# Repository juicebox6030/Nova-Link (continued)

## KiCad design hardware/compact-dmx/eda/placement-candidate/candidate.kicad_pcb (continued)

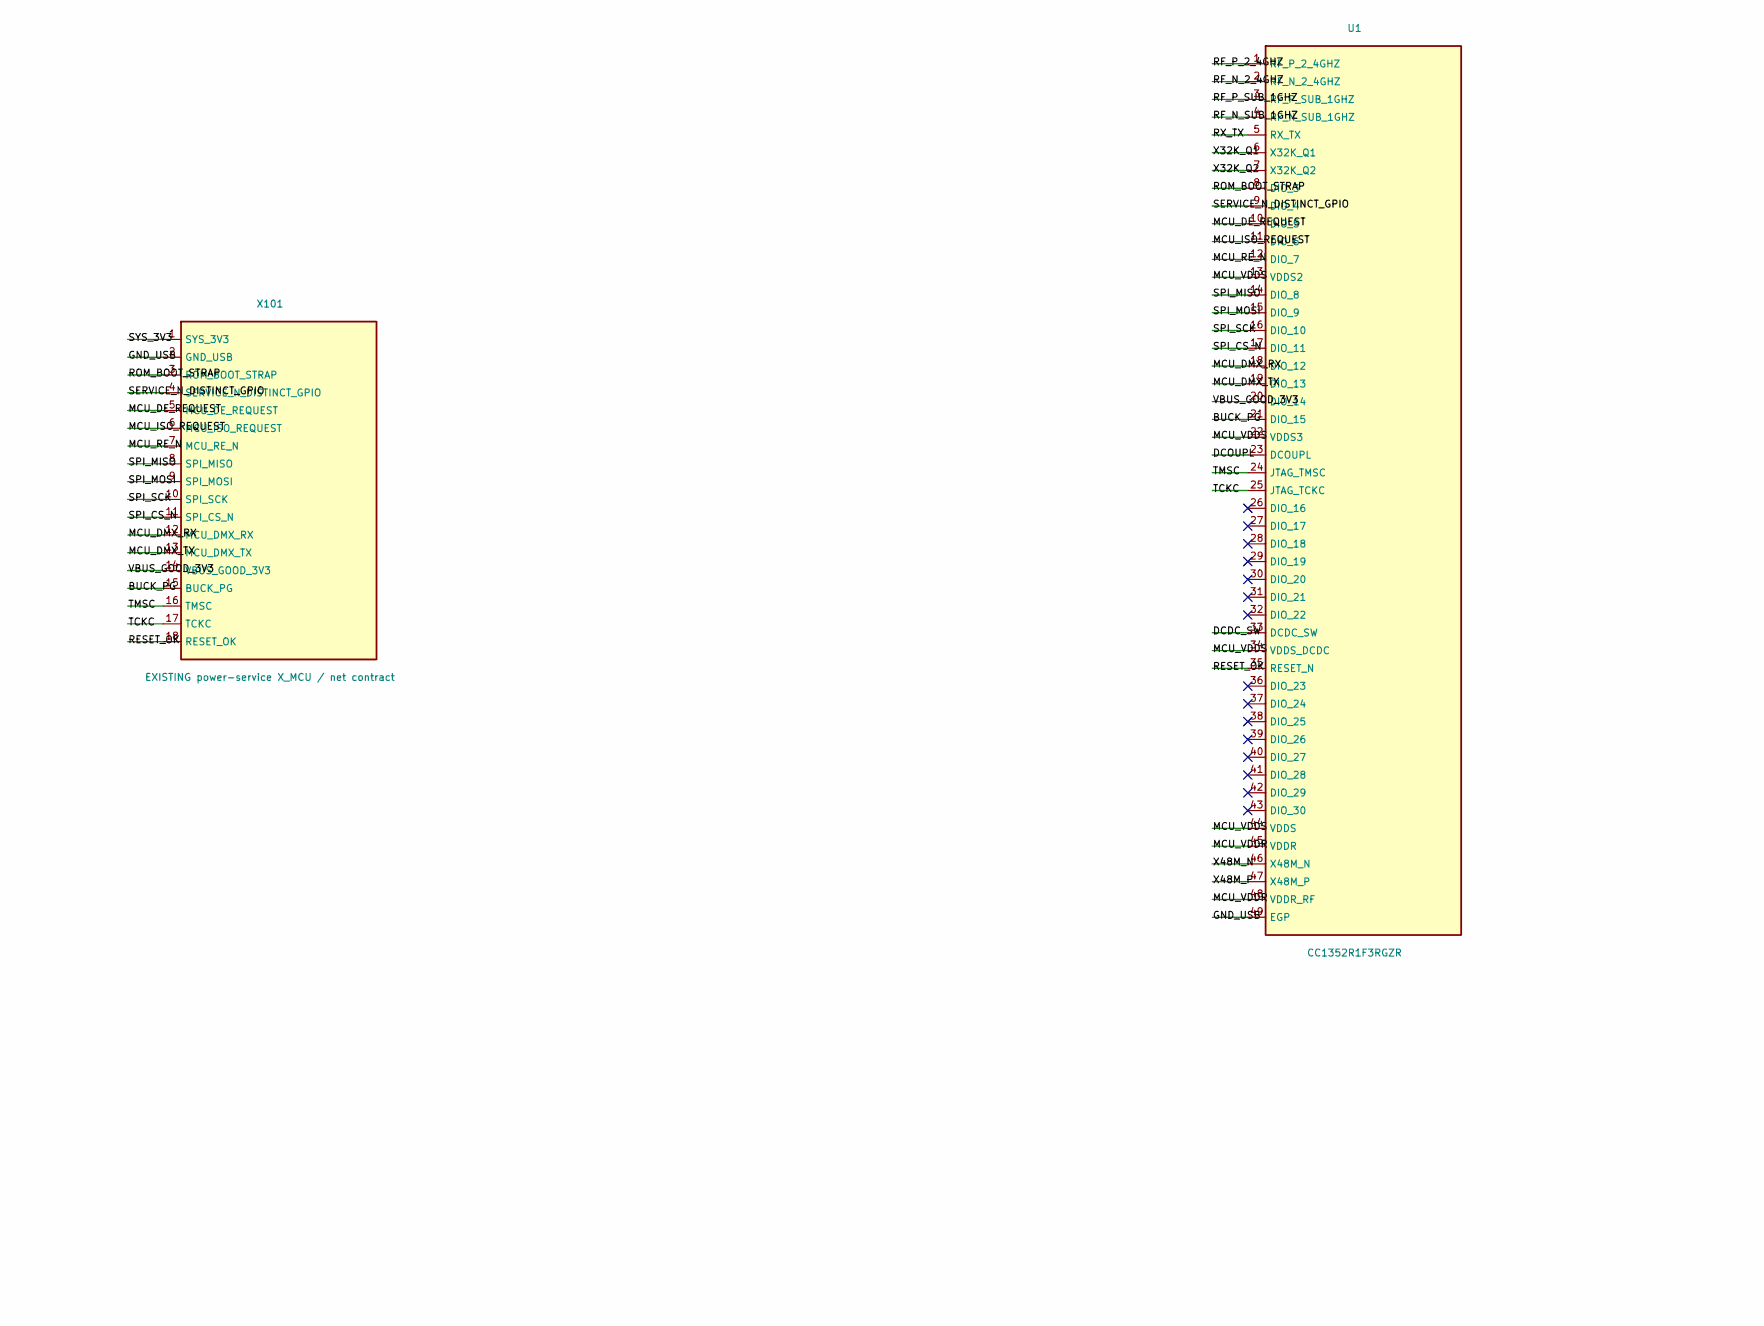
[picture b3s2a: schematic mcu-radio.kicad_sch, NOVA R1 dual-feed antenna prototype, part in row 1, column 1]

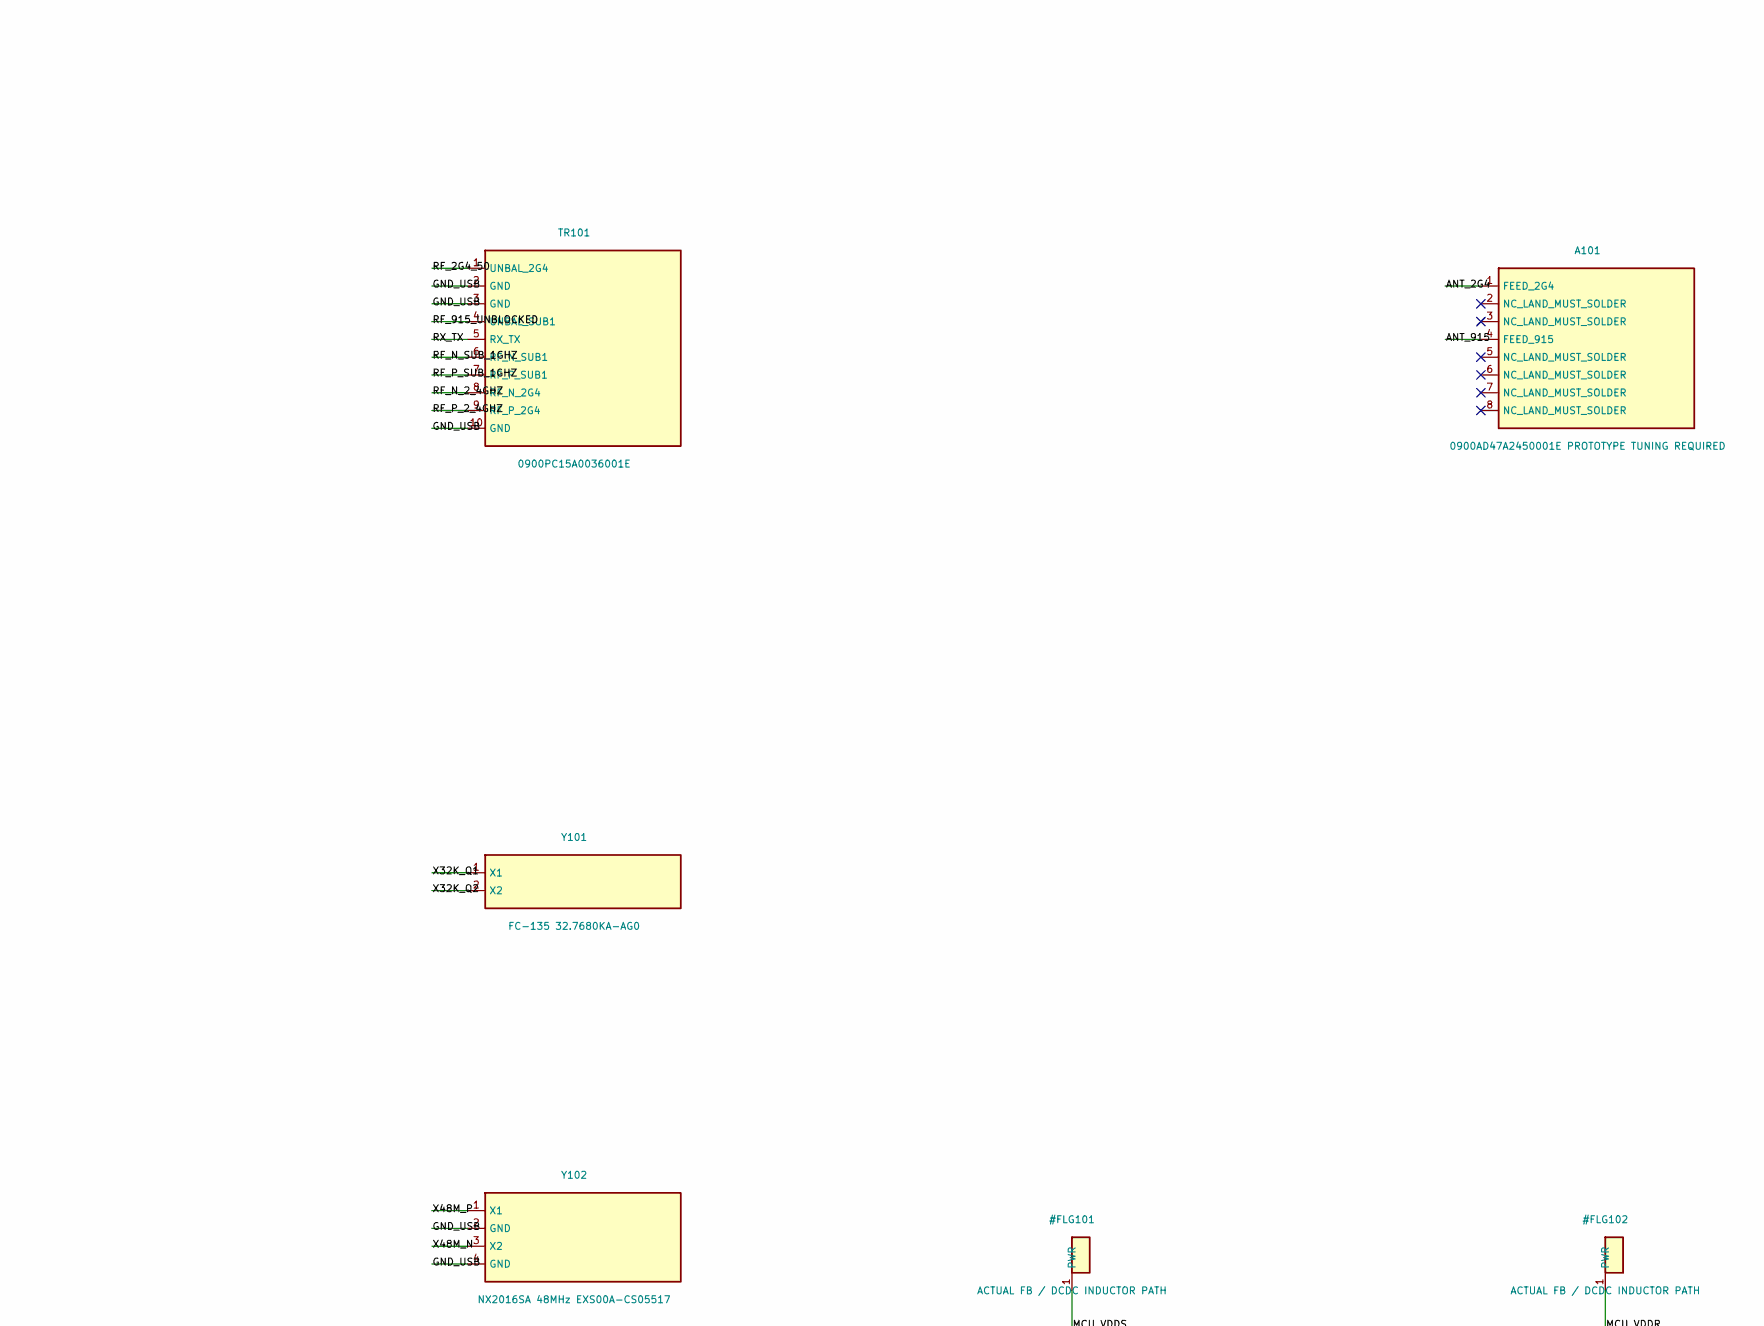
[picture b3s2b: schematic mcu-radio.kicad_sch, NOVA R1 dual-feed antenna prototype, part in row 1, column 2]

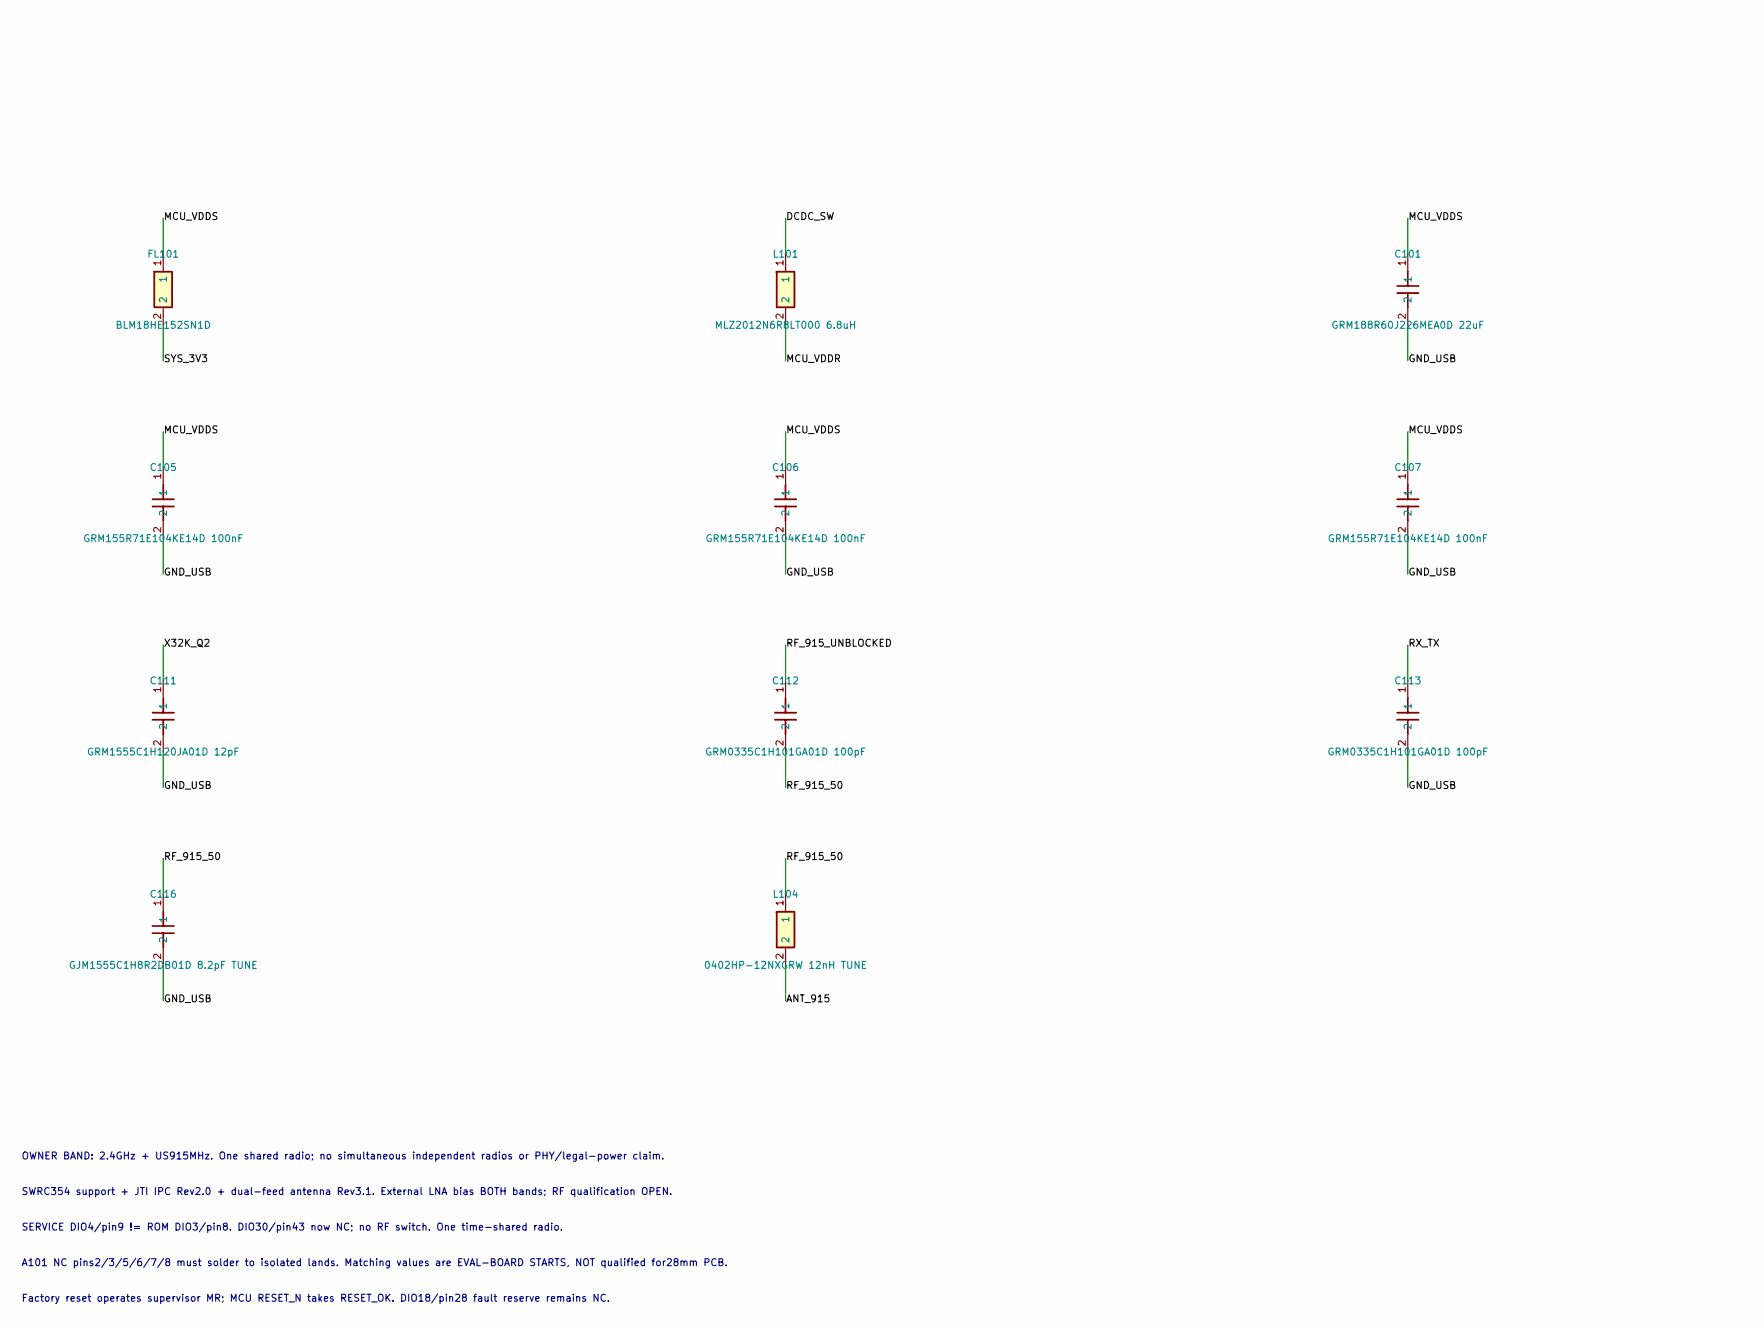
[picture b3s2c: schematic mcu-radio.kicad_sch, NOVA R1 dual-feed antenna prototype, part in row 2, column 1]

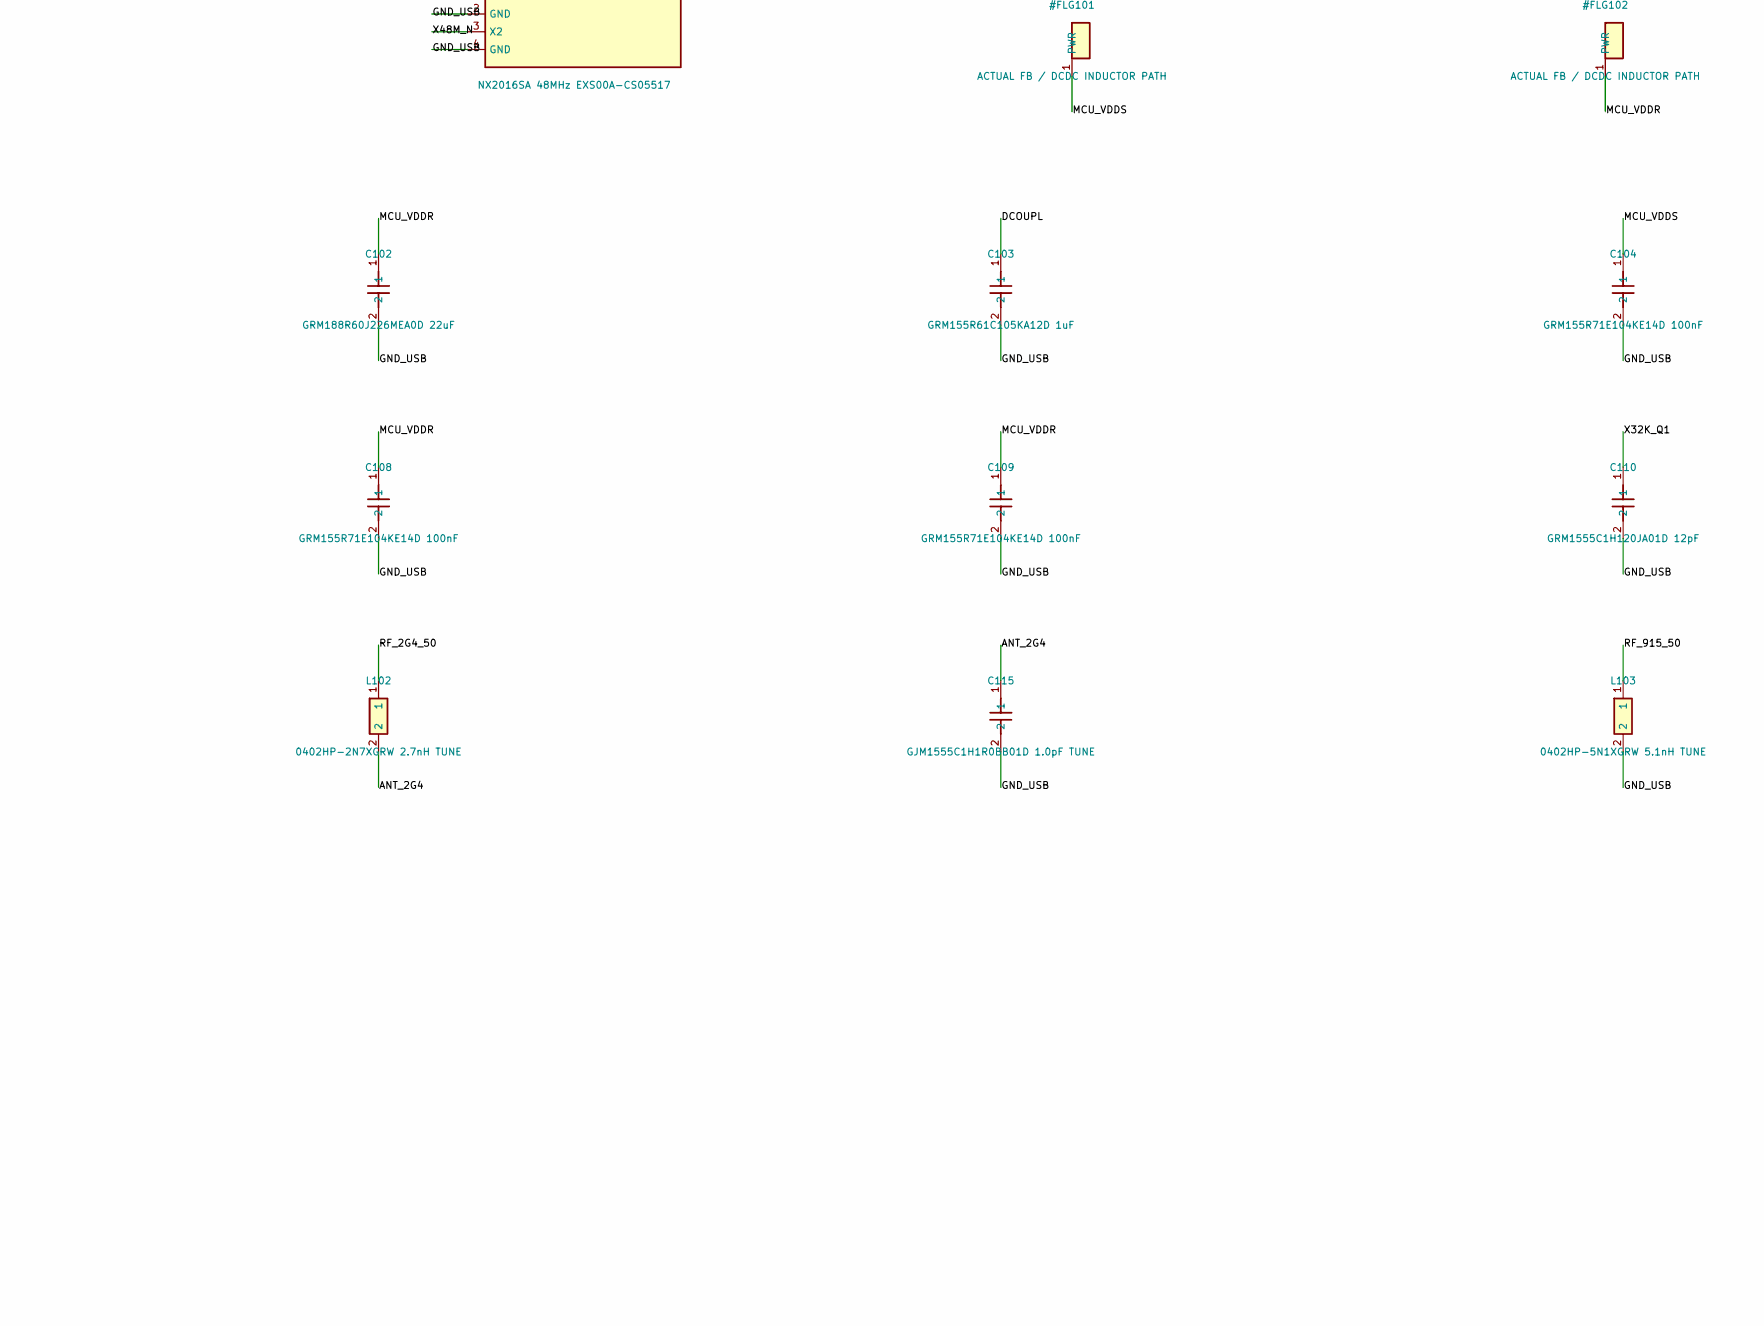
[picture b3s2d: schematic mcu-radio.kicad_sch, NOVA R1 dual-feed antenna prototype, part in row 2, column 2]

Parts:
A101: 0900AD47A2450001E PROTOTYPE TUNING REQUIRED; Johanson_0900AD47_IsolatedLands
C101, C102: GRM188R60J226MEA0D 22uF; TI_CAPC1608_Vector
C103: GRM155R61C105KA12D 1uF; TI_CAPC1005_Vector
C104, C105, C106, C107, C108, C109: GRM155R71E104KE14D 100nF; TI_CAPC1005_Vector
C110, C111: GRM1555C1H120JA01D 12pF; TI_CAPC1005_Vector
C112, C113: GRM0335C1H101GA01D 100pF; TI_CAPC0603_Vector
C115: GJM1555C1H1R0BB01D 1.0pF TUNE; Murata_GJM155_Manufacturer
C116: GJM1555C1H8R2DB01D 8.2pF TUNE; Murata_GJM155_Manufacturer
FL101: BLM18HE152SN1D; TI_BLM18_Vector
L101: MLZ2012N6R8LT000 6.8uH; TI_MLZ2012_Vector
L102: 0402HP-2N7XGRW 2.7nH TUNE; Coilcraft_0402HP_Manufacturer
L103: 0402HP-5N1XGRW 5.1nH TUNE; Coilcraft_0402HP_Manufacturer
L104: 0402HP-12NXGRW 12nH TUNE; Coilcraft_0402HP_Manufacturer
TR101: 0900PC15A0036001E; TI_IPC1352_Vector
U1: CC1352R1F3RGZR; TI_RGZ0048A
X101: EXISTING power-service X_MCU / net contract
Y101: FC-135 32.7680KA-AG0; Epson_FC135_Manufacturer
Y102: NX2016SA 48MHz EXS00A-CS05517; NDK_NX2016SA_Manufacturer

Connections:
ANT_2G4: A101.1 (FEED_2G4), C115.1, L102.2
ANT_915: A101.4 (FEED_915), L104.2
BUCK_PG: U1.21 (DIO_15), X101.15 (BUCK_PG)
DCDC_SW: L101.1, U1.33 (DCDC_SW)
DCOUPL: C103.1, U1.23 (DCOUPL)
GND_USB: C101.2, C102.2, C103.2, C104.2, C105.2, C106.2, C107.2, C108.2, C109.2, C110.2, C111.2, C113.2, C115.2, C116.2, L103.2, TR101.2 (GND), TR101.3 (GND), TR101.10 (GND), U1.49 (EGP), X101.2 (GND_USB), Y102.2 (GND), Y102.4 (GND); also elsewhere on the board
MCU_DE_REQUEST: U1.10 (DIO_5), X101.5 (MCU_DE_REQUEST)
MCU_DMX_RX: U1.18 (DIO_12), X101.12 (MCU_DMX_RX); also elsewhere on the board
MCU_DMX_TX: U1.19 (DIO_13), X101.13 (MCU_DMX_TX); also elsewhere on the board
MCU_ISO_REQUEST: U1.11 (DIO_6), X101.6 (MCU_ISO_REQUEST)
MCU_RE_N: U1.12 (DIO_7), X101.7 (MCU_RE_N); also elsewhere on the board
MCU_VDDR: C102.1, C108.1, C109.1, L101.2, U1.45 (VDDR), U1.48 (VDDR_RF)
MCU_VDDS: C101.1, C104.1, C105.1, C106.1, C107.1, FL101.1, U1.13 (VDDS2), U1.22 (VDDS3), U1.34 (VDDS_DCDC), U1.44 (VDDS)
RESET_OK: U1.35 (RESET_N), X101.18 (RESET_OK)
RF_2G4_50: L102.1, TR101.1 (UNBAL_2G4)
RF_915_50: C112.2, C116.1, L103.1, L104.1
RF_915_UNBLOCKED: C112.1, TR101.4 (UNBAL_SUB1)
RF_N_2_4GHZ: TR101.8 (RF_N_2G4), U1.2 (RF_N_2_4GHZ)
RF_N_SUB_1GHZ: TR101.6 (RF_N_SUB1), U1.4 (RF_N_SUB_1GHZ)
RF_P_2_4GHZ: TR101.9 (RF_P_2G4), U1.1 (RF_P_2_4GHZ)
RF_P_SUB_1GHZ: TR101.7 (RF_P_SUB1), U1.3 (RF_P_SUB_1GHZ)
ROM_BOOT_STRAP: U1.8 (DIO_3), X101.3 (ROM_BOOT_STRAP)
RX_TX: C113.1, TR101.5 (RX_TX), U1.5 (RX_TX)
SERVICE_N_DISTINCT_GPIO: U1.9 (DIO_4), X101.4 (SERVICE_N_DISTINCT_GPIO)
SPI_CS_N: U1.17 (DIO_11), X101.11 (SPI_CS_N)
SPI_MISO: U1.14 (DIO_8), X101.8 (SPI_MISO)
SPI_MOSI: U1.15 (DIO_9), X101.9 (SPI_MOSI)
SPI_SCK: U1.16 (DIO_10), X101.10 (SPI_SCK)
SYS_3V3: FL101.2, X101.1 (SYS_3V3); also elsewhere on the board
TCKC: U1.25 (JTAG_TCKC), X101.17 (TCKC)
TMSC: U1.24 (JTAG_TMSC), X101.16 (TMSC)
VBUS_GOOD_3V3: U1.20 (DIO_14), X101.14 (VBUS_GOOD_3V3)
X32K_Q1: C110.1, U1.6 (X32K_Q1), Y101.1 (X1)
X32K_Q2: C111.1, U1.7 (X32K_Q2), Y101.2 (X2)
X48M_N: U1.46 (X48M_N), Y102.3 (X2)
X48M_P: U1.47 (X48M_P), Y102.1 (X1)
mcu-radio_unconnected-(A101-NC_LAND_MUST_SOLDER-Pad2): A101.2 (NC_LAND_MUST_SOLDER)
mcu-radio_unconnected-(A101-NC_LAND_MUST_SOLDER-Pad3): A101.3 (NC_LAND_MUST_SOLDER)
mcu-radio_unconnected-(A101-NC_LAND_MUST_SOLDER-Pad5): A101.5 (NC_LAND_MUST_SOLDER)
mcu-radio_unconnected-(A101-NC_LAND_MUST_SOLDER-Pad6): A101.6 (NC_LAND_MUST_SOLDER)
mcu-radio_unconnected-(A101-NC_LAND_MUST_SOLDER-Pad7): A101.7 (NC_LAND_MUST_SOLDER)
mcu-radio_unconnected-(A101-NC_LAND_MUST_SOLDER-Pad8): A101.8 (NC_LAND_MUST_SOLDER)
mcu-radio_unconnected-(U1-DIO_16-Pad26): U1.26 (DIO_16)
mcu-radio_unconnected-(U1-DIO_17-Pad27): U1.27 (DIO_17)
mcu-radio_unconnected-(U1-DIO_18-Pad28): U1.28 (DIO_18)
mcu-radio_unconnected-(U1-DIO_19-Pad29): U1.29 (DIO_19)
mcu-radio_unconnected-(U1-DIO_20-Pad30): U1.30 (DIO_20)
mcu-radio_unconnected-(U1-DIO_21-Pad31): U1.31 (DIO_21)
mcu-radio_unconnected-(U1-DIO_22-Pad32): U1.32 (DIO_22)
mcu-radio_unconnected-(U1-DIO_23-Pad36): U1.36 (DIO_23)
mcu-radio_unconnected-(U1-DIO_24-Pad37): U1.37 (DIO_24)
mcu-radio_unconnected-(U1-DIO_25-Pad38): U1.38 (DIO_25)
mcu-radio_unconnected-(U1-DIO_26-Pad39): U1.39 (DIO_26)
mcu-radio_unconnected-(U1-DIO_27-Pad40): U1.40 (DIO_27)
mcu-radio_unconnected-(U1-DIO_28-Pad41): U1.41 (DIO_28)
mcu-radio_unconnected-(U1-DIO_29-Pad42): U1.42 (DIO_29)
mcu-radio_unconnected-(U1-DIO_30-Pad43): U1.43 (DIO_30)

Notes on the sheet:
OWNER BAND: 2.4GHz + US915MHz. One shared radio; no simultaneous independent radios or PHY/legal-power claim.
SWRC354 support + JTI IPC Rev2.0 + dual-feed antenna Rev3.1. External LNA bias BOTH bands; RF qualification OPEN.
SERVICE DIO4/pin9 != ROM DIO3/pin8. DIO30/pin43 now NC; no RF switch. One time-shared radio.
A101 NC pins2/3/5/6/7/8 must solder to isolated lands. Matching values are EVAL-BOARD STARTS, NOT qualified for28mm PCB.
Factory reset operates supervisor MR; MCU RESET_N takes RESET_OK. DIO18/pin28 fault reserve remains NC.

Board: 2 copper layers, 41 parts (0 on the bottom side), 31 nets, no tracks yet.

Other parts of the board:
H1, H2, H3, H4: Mechanical NPTH 2.2

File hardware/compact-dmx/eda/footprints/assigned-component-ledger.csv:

sheet_reference,selected_MPN_value,footprint,approval_status
dmx.C1,GRM155R71E104KE14D 100nF 25V X7R,NOVA_HW:TI_CAPC1005_Vector,SOURCE_DIMENSIONED_REFERENCE_OR_MANUFACTURER_LAND
dmx.C2,GRM21BR71A106KE51L 10uF 10V X7R,NOVA_HW:Murata_GRM21_Reflow,SOURCE_DIMENSIONED_REFERENCE_OR_MANUFACTURER_LAND
dmx.C3,GRM155R71E104KE14D 100nF 25V X7R,NOVA_HW:TI_CAPC1005_Vector,SOURCE_DIMENSIONED_REFERENCE_OR_MANUFACTURER_LAND
dmx.C4,GRM21BR71A106KE51L 10uF 10V X7R,NOVA_HW:Murata_GRM21_Reflow,SOURCE_DIMENSIONED_REFERENCE_OR_MANUFACTURER_LAND
dmx.R1,CRCW040210K0FKED 10k 1%,NOVA_HW:Vishay_CRCW0402,SOURCE_DIMENSIONED_REFERENCE_OR_MANUFACTURER_LAND
dmx.R2,CRCW040210K0FKED 10k 1%,NOVA_HW:Vishay_CRCW0402,SOURCE_DIMENSIONED_REFERENCE_OR_MANUFACTURER_LAND
dmx.R3,CRCW040210K0FKED 10k 1%,NOVA_HW:Vishay_CRCW0402,SOURCE_DIMENSIONED_REFERENCE_OR_MANUFACTURER_LAND
dmx.R4,CRCW04021K00FKED 1k 1%,NOVA_HW:Vishay_CRCW0402,SOURCE_DIMENSIONED_REFERENCE_OR_MANUFACTURER_LAND
dmx.R_TERM1,CRCW1206240RFKEA 240R 1% 0.25W,NOVA_HW:Vishay_CRCW1206,SOURCE_DIMENSIONED_REFERENCE_OR_MANUFACTURER_LAND
dmx.R_TERM2,CRCW1206240RFKEA 240R 1% 0.25W,NOVA_HW:Vishay_CRCW1206,SOURCE_DIMENSIONED_REFERENCE_OR_MANUFACTURER_LAND
dmx.S_TERM,PCM12SMTR OFF=1-2 / ON=2-3,NOVA_HW:PCM12_PENDING_MANUFACTURER_LAND_RECHECK,PARENT_OWNS_SWITCH_VISUAL_CHECK_LIFECYCLE_UNVERIFIED
dmx.U5,ISOW1412DFMR,NOVA_HW:TI_DFM0020A,SOURCE_DIMENSIONED_REFERENCE_OR_MANUFACTURER_LAND
mcu-radio.A101,0900AD47A2450001E PROTOTYPE TUNING REQUIRED,NOVA_HW:Johanson_0900AD47_IsolatedLands,SOURCE_DIMENSIONED_REFERENCE_OR_MANUFACTURER_LAND
mcu-radio.C101,GRM188R60J226MEA0D 22uF,NOVA_HW:TI_CAPC1608_Vector,SOURCE_DIMENSIONED_REFERENCE_OR_MANUFACTURER_LAND
mcu-radio.C102,GRM188R60J226MEA0D 22uF,NOVA_HW:TI_CAPC1608_Vector,SOURCE_DIMENSIONED_REFERENCE_OR_MANUFACTURER_LAND
mcu-radio.C103,GRM155R61C105KA12D 1uF,NOVA_HW:TI_CAPC1005_Vector,SOURCE_DIMENSIONED_REFERENCE_OR_MANUFACTURER_LAND
mcu-radio.C104,GRM155R71E104KE14D 100nF,NOVA_HW:TI_CAPC1005_Vector,SOURCE_DIMENSIONED_REFERENCE_OR_MANUFACTURER_LAND
mcu-radio.C105,GRM155R71E104KE14D 100nF,NOVA_HW:TI_CAPC1005_Vector,SOURCE_DIMENSIONED_REFERENCE_OR_MANUFACTURER_LAND
mcu-radio.C106,GRM155R71E104KE14D 100nF,NOVA_HW:TI_CAPC1005_Vector,SOURCE_DIMENSIONED_REFERENCE_OR_MANUFACTURER_LAND
mcu-radio.C107,GRM155R71E104KE14D 100nF,NOVA_HW:TI_CAPC1005_Vector,SOURCE_DIMENSIONED_REFERENCE_OR_MANUFACTURER_LAND
mcu-radio.C108,GRM155R71E104KE14D 100nF,NOVA_HW:TI_CAPC1005_Vector,SOURCE_DIMENSIONED_REFERENCE_OR_MANUFACTURER_LAND
mcu-radio.C109,GRM155R71E104KE14D 100nF,NOVA_HW:TI_CAPC1005_Vector,SOURCE_DIMENSIONED_REFERENCE_OR_MANUFACTURER_LAND
mcu-radio.C110,GRM1555C1H120JA01D 12pF,NOVA_HW:TI_CAPC1005_Vector,SOURCE_DIMENSIONED_REFERENCE_OR_MANUFACTURER_LAND
mcu-radio.C111,GRM1555C1H120JA01D 12pF,NOVA_HW:TI_CAPC1005_Vector,SOURCE_DIMENSIONED_REFERENCE_OR_MANUFACTURER_LAND
mcu-radio.C112,GRM0335C1H101GA01D 100pF,NOVA_HW:TI_CAPC0603_Vector,SOURCE_DIMENSIONED_REFERENCE_OR_MANUFACTURER_LAND
mcu-radio.C113,GRM0335C1H101GA01D 100pF,NOVA_HW:TI_CAPC0603_Vector,SOURCE_DIMENSIONED_REFERENCE_OR_MANUFACTURER_LAND
mcu-radio.C115,GJM1555C1H1R0BB01D 1.0pF TUNE,NOVA_HW:Murata_GJM155_Manufacturer,SOURCE_DIMENSIONED_MANUFACTURER_LAND_PROTOTYPE_RF_RETUNE
mcu-radio.C116,GJM1555C1H8R2DB01D 8.2pF TUNE,NOVA_HW:Murata_GJM155_Manufacturer,SOURCE_DIMENSIONED_MANUFACTURER_LAND_PROTOTYPE_RF_RETUNE
mcu-radio.FL101,BLM18HE152SN1D,NOVA_HW:TI_BLM18_Vector,SOURCE_DIMENSIONED_REFERENCE_OR_MANUFACTURER_LAND
mcu-radio.L101,MLZ2012N6R8LT000 6.8uH,NOVA_HW:TI_MLZ2012_Vector,SOURCE_DIMENSIONED_REFERENCE_OR_MANUFACTURER_LAND
mcu-radio.L102,0402HP-2N7XGRW 2.7nH TUNE,NOVA_HW:Coilcraft_0402HP_Manufacturer,SOURCE_DIMENSIONED_MANUFACTURER_LAND_PROTOTYPE_RF_RETUNE
mcu-radio.L103,0402HP-5N1XGRW 5.1nH TUNE,NOVA_HW:Coilcraft_0402HP_Manufacturer,SOURCE_DIMENSIONED_MANUFACTURER_LAND_PROTOTYPE_RF_RETUNE
mcu-radio.L104,0402HP-12NXGRW 12nH TUNE,NOVA_HW:Coilcraft_0402HP_Manufacturer,SOURCE_DIMENSIONED_MANUFACTURER_LAND_PROTOTYPE_RF_RETUNE
mcu-radio.TR101,0900PC15A0036001E,NOVA_HW:TI_IPC1352_Vector,SOURCE_DIMENSIONED_REFERENCE_OR_MANUFACTURER_LAND
mcu-radio.U1,CC1352R1F3RGZR,NOVA_HW:TI_RGZ0048A,SOURCE_DIMENSIONED_REFERENCE_OR_MANUFACTURER_LAND
mcu-radio.Y101,FC-135 32.7680KA-AG0,NOVA_HW:Epson_FC135_Manufacturer,SOURCE_DIMENSIONED_REFERENCE_OR_MANUFACTURER_LAND
mcu-radio.Y102,NX2016SA 48MHz EXS00A-CS05517,NOVA_HW:NDK_NX2016SA_Manufacturer,SOURCE_DIMENSIONED_REFERENCE_OR_MANUFACTURER_LAND

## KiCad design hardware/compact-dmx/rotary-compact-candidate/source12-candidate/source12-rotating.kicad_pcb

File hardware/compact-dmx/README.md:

# NOVA compact hardware revision B — RFQ / DFM package

Canonical requirements, correction history, sources and release gates:
[design](../../docs/hardware/DMX_Dongle_and_Power_Barrel.md).
This is an **unreleased prototype-development package**, not production instructions.

Latest owner requirement: normal operation needs a5V USB-C source advertising
at least1.5A, including the NOVA-LINK barrel. Existing Rev C and the completed
`eda/power-service/separated-candidate/` capture use the superseded500mA basis.
They are retained comparison designs, not implementations of the new source
qualification. The [qualified-source candidate](eda/power-service/qualified15-candidate/DESIGN.md)
captures hardware CC qualification and separate charger/backup circuitry.
Parent checks confirm zero ERC violations and nominal two-sided placement of
all137 candidate footprints alongside the original37 parts, within the proposed
flush-port board outline. DRC reports0 geometric violations and452 unrouted
connections. Its749.96mm² core courtyard sum exceeds the old150mm² reservation;
the existing case is unchanged. The explicit aged-ESR example provides9.73s,
below the10s requirement. Startup, cell-fault protection, thermal behavior and
routing remain open. The review's startup-blocking U40 mux-mode connection is
corrected to TI's MODE=VIN1 priority configuration. Parent verified the one-pad
net change, fresh KiCad exports and source-table regressions reproducing both
original failures. Physical startup and source-transition acceptance remain
open. This separate candidate is not included in baseline package acceptance.

The [25F buffer proposal](eda/buffer-fit-candidate/README.md) is the selected
development basis for addressing the15F runtime shortfall. A local PCB aperture
and lower cradle retain the98×34×24mm case; independent checks reproduce16.34s
under the stated aged-capacitance/ESR and efficiency assumptions. Nominal25mA
recharge takes43.3min before tail. The [editable assembly prototype](eda/buffer-fit-candidate/integrated25/README.md)
has a real rounded PCB aperture, proposed formed leads/lands, liners and positive
lid retention. Parent saved-board/CAD checks pass; allocated cell/PCB clearance
is0.178mm. Lead forming, vent path, solder/process and retention strength remain
unqualified. [Independent cell protection](eda/cell-protection-candidate/DESIGN.md)
is captured separately. The bounded GLM review found no new electrical defects;
its sole citation correction is recorded in the canonical hardware checkpoint.
The conditional hot-fuse screen is13.26s,
with interruption/clearing bounds still open. The [protected25 integration](eda/buffer-fit-candidate/protected25-placement/README.md)
places the14 added parts and merges the actual power/protection schematic.
Parent fresh CLI checks give ERC0/DRC0 with485 unconnected items;40 saved closed
solids/780 pairs pass nominal geometry. Fit requires a proposed0.40mm local base
relief, leaving1.60mm floor within the unchanged external envelope. Strength,
unfused routing and process capability are unqualified. Focused independent
review hit the provider rate limit and remains pending. Routing, cold/runtime
measurements and manufacturing qualification remain open.

The [repaired rotary collar](rotary-compact-candidate/mechanism-repaired/README.md)
passes its geometric prototype checks atØ66×67.8mm locked/72.0mm released.
Parent reopened43 connected solids and recomputed741 neutral component pairs
without unintended intersections. The [routed axial USB source](rotary-compact-candidate/source-axial-routing/DESIGN.md)
is27×20×1mm with no unconnected items and four retained connector hole-clearance
errors. The [actual-board collar integration](rotary-compact-candidate/collar-source-integrated/README.md)
isØ66mm,73.17mm locked/77.37mm released, with captured board retention and
static flex fanout. Its added resistance fails the previous stress-current
screen:3.022A versus2.995A breaker floor before the stationary wire allocation.
The [stationary carrier prototype](rotary-compact-candidate/stationary-irm20-integration/DESIGN.md)
closes the static lead/trunk clash, but pin-to-land solder process, in-core wire
assembly remain unresolved. The [installation-source gate](rotary-compact-candidate/stationary-irm20-integration/installation-gate/receipt.json)
blocks IRM20 in theØ43mm bore for production: the published lateral allowance
alone needs47.7mm, with no explicit alternative construction found in the three
reviewed official PDFs. R1 jig/assembly development stops. The bounded
[alternative-supply comparison](rotary-compact-candidate/power-architecture-screen/README.md)
found no supported tight construction for either alternative. A stationary
source-pod allocation honoring the published spacing is checked at330×89×72mm,
which fails the compactness objective. Its43 native solids and three STEP
exports reopen, but carrier retention and terminal/FPC transitions are incomplete.
See the [allocation comparison](rotary-compact-candidate/stationary-source-pod/README.md).
The [combined compact comparison](rotary-compact-candidate/combined-compact-allocation/README.md)
shortens the old-source layout to270×89×72mm but fails integration: eight
physical interferences and a0.581mm tail gap remain. The new S12 clamp exceeds
Ø66 under the screened transform. The subsequent
[CIR-R1 interface repair](rotary-compact-candidate/compact-interface-repair/README.md)
incorporates both unchanged S12 boards at a trialØ70 collar with explicit
retention, fanout and tool access. Its bounded nominal geometry checks pass;
275×91×74mm remains a comparison with incomplete source-carrier/connector ends,
not an accepted compact product envelope. The
[S12-R1 circuit](rotary-compact-candidate/source12-candidate/DESIGN.md) is captured
on32×26mm rotating/24×16mm stationary unrouted boards. Parent fresh ERC is0;
DRC retains four connector findings and120/22 unrouted connections. Conditional
port voltage is4.783–5.304V with179mA modeled input-breaker margin; maximum USB
fault voltage/energy remains unproved. The [bounded protection pass](rotary-compact-candidate/source12-protection-energy/README.md)
screened two remedies without establishing an acceptable network; no new circuit
was captured. Its named source, response and energy requirements remain prerequisites
to source routing. This does not establish impossibility of all protection designs.
CIR-R1 provides nominal mechanical integration of these boards, but no accepted
complete pod/mains construction. Do not apply12V to the retained5V board;
electrical and manufacturing acceptance remain open.
The [CYL-R1 cylindrical screen](rotary-compact-candidate/cylindrical-source-repack/README.md)
stops at phase0 HOLD without new assembly CAD. Parent checks reproduce the
film failure and find a larger finite3D clearance-corridor interference than
the radial-only screen. The original comparison used unequal connector/tool
allowances; a matched-allowance sensitivity still suggests potential reduction,
not an accepted envelope. The [CYL-R2 constructed partial prototype](rotary-compact-candidate/cylindrical-source-repair/README.md)
now clears the corrected finite corridor and film checks. Parent native CAD
checks reproduce356 valid closed objects,0.4876mm minimum corridor distance and
0.3742mm film clearance in the allocated bore. Its302.8×77×77mm matched classic
planning comparison is not finished product size. Neck attachments, fuse and
terminals are unbuilt; mounting/lead/film crossings of the source installation
reservation remain unapproved. The completed GLM Flash review found one
assembly defect: the installed upper shell blocks all four closure-driver
paths. [CAF-R1](rotary-compact-candidate/closure-access-fix/README.md) removes
those overlaps; parent [CAF-R2](rotary-compact-candidate/closure-access-margin-fix/README.md)
also removes an accidental zero-clearance ledge contact. Four Ø5.5 passages now
provide0.25mm nominal tool-to-upper clearance, preserving all four bearing seats,
355 other shapes and all placements. Ports, strength and sealing remain
unqualified. Original reviewed files stay unchanged. See the canonical checkpoint
for checks. The completed [two-reference source screen](rotary-compact-candidate/compact-source-reference-screen/README.md)
establishes no smaller complete replacement. TIDA-01560 remains a conditional
12V reference only:66×50mm board, complete height unknown,1.125A rating below
the retained overload screen. Existing source circuits and CAD remain unchanged.
No delegated work is active and no manufacturing release is claimed.
These prototypes do not establish a manufacturable barrel. Source startup,
current delivery, sealed thermal behavior, USB and endurance remain unqualified.

The [manufacturer connector contracts](connector-interface-candidate/README.md)
provide12 original STEP references. Selected classic rear depths are30.4mm;
TRUE1 inlet/outlet31.2/32.8mm, all before terminals/wire access. The examined
NEMA flanged pair needsØ63.5mm and45.3/43.6mm rear depths, so it is not a drop-in
Ø48×24mm end. Parent checked original model identities, mounting shoulders and
source hashes; installed mated lengths and approved molded NEMA cords remain open.
Vendor invalid/open models are reference geometry, not collision-acceptance solids.
The [installed-mating study](connector-mating-envelope/README.md) ends in HOLD
for all four Neutrik pairs: mounting shoulders and isolated face probes do not
establish seating depth or locked/latch clearance. Its58 inventory/233 direct
protected-input hashes pass parent checks; no paired CAD or complete fit is claimed.

The [partial PCB placement](eda/placement-candidate/README.md) places37 MCU/RF/DMX
parts on the90×28mm outline. Parent verified the corrected signal-net merges and
candidate isolation partition. KiCad reports zero default geometric violations
and89 unconnected items; the board has no routing and omits power/SPI/USB/service
hardware. It does not establish complete-board packing or manufacturing readiness.

A separate [39-part USB/NOR copy](eda/service-footprints/gct-power-candidate/README.md)
adds proposed GCTUSB4125-GF-A and staging-flash footprints: fresh parent KiCad
DRC reports zero geometric violations and103 unrouted connections. It preserves
the original37 parts, but still needs PCB-thickness/process qualification,
removal of the obsolete midmount notch and resolution of a3mm case recess.
The active BOM, board and enclosure remain unchanged by that proposal.

The [flush-port mechanical prototype](eda/service-footprints/gct-power-candidate/mechanical/README.md)
adds a12.4×2.3mm PCB tongue and moves the USB connector3mm forward, making its
mating face nominally flush while retaining the98×34×24mm case. Independent
saved-CAD and board checks pass; component-height keepouts from the new support
must be respected in power placement. Compliant supports, strength, exact cable
fit and manufacturing process remain unqualified. This is a separate proposal,
not an adopted product outline or manufacturing release.

## Files and regeneration

From repository root, with existing tools only:

```sh
/home/juicebox/.local/bin/freecadcmd hardware/compact-dmx/cad/build_cad.py
python3 hardware/compact-dmx/cad/make_drawings.py
python3 hardware/compact-dmx/eda/generate_dmx_sheet.py
python3 hardware/compact-dmx/eda/verify_kicad.py
python3 hardware/compact-dmx/validate_package.py
```

Verified local tools: FreeCAD 1.1.3, existing user Flatpak KiCad 10.0.7
(`flatpak run --command=kicad-cli org.kicad.KiCad`), and LibreDWG 0.14 installed
with owner approval at `.tools/libredwg-0.14/bin/`. The `.tools/` directory is
ignored by Git. LibreDWG source/archive provenance is in the canonical checkpoint;
conversion warnings must be assessed before using any converted fixture geometry.

- `cad/build_cad.py`: editable dimension-driven FreeCAD construction source, analytic
  B-rep solids. Dimensions sheet in FCStd is an informational summary; edit source
  parameters and regenerate. It is not a live spreadsheet-driven constraint tree.
- `exports/compact-dmx-revb.FCStd`: editable FreeCAD document; source remains the
  authoritative parametric construction recipe.
- `exports/*assembly.step`, `barrel-exploded.step`: supplier bounding envelopes plus
  custom RFQ solids; not supplier-approved connector models. Exploded offsets are
  for visualization only, not installed locations.
- `exports/D01*`, `D02*`, `B01*`, `B04*`, `B06*`, `B09*`, `B12*`, `B19*`: individual custom-part STEP.
  No STL/mesh is represented as a production surface.
- `exports/01*.svg` through `03*.svg`, `manufacturer-drawings.pdf`: three dimensioned
  vector drawing sheets; source is `cad/make_drawings.py`.
- `exports/sidecar-pcb-outline.dxf`: outline, mounting holes and provisional USB edge slot only, no copper/footprints.
  `lock-ring.dxf`: proposed index-ring profile/holes, not released CAM.
- `eda/dmx-interface.kicad_sch`: modern self-contained schematic with embedded,
  electrically typed symbols; matching `nova-dmx.kicad_sym`, project and local
  symbol table preserve library checking. Twelve circuit components plus X1/J1
  explicit partial-sheet boundaries. X1 maps to the current `eda/power-service/` X_DMX interface.
  Power, cutoff and POR gating are captured there; MCU/RF have a separate captured sheet. Pin8 is modeled in enable-input mode;
  the alternate open-drain fault-output mode is documented on the sheet.
- `eda/verify_kicad.py`: invokes existing Flatpak KiCad10.0.7 to export the actual
  XML netlist, PDF/SVG and run ERC with all severities and failure exit enabled.
  It verifies every U5 pin/type and every resistor/capacitor node against the CLI
  export. `dmx-interface.net` is now ONLY a real KiCad-generated netlist.
- `eda/dmx-erc.json` and `kicad-validation.json`: zero errors/warnings/exclusions
  on this PARTIAL sheet;14 exported components/15 nets, including boundaries
  and intentional NC nodes.
  These results do not establish complete product capture, PCB DRC or hardware
  operation. `eda/dmx-interface.pdf` / `rendered/dmx-interface.svg` are CLI renders.
- Correction: the retired legacy `.sch`/cache loaded zero components in KiCad;
  its hand-written XML was not evidence of schematic connectivity. Prior PATH-only
  discovery missed the existing KiCad Flatpak. Both legacy files are removed.
- `exports/cad-validation.json`: major-package interference, solid validity, explicit base/PCB contact, package/PCB and shell clearance, antenna-volume checks,
  78 neutral barrel mechanical pairs, minimum/nominal/maximum lock release,
  and 181-angle ideal two-lane wire-to-lock-sleeve clearance.
  Includes allocated zones; does not prove complete component packing, whole-part
  assembly clearance, wire motion, fixture fit or mains insulation compliance.

The STEP files deliberately include uncut mains endcap blanks. Source-backed
connector cutouts, detailed primary harness, captive lock slider/spring/hood,
fasteners and closed secondary cassette still need modeled detail and engineering
review. B19 is a modeled sleeve through the cassette; divider/cover seals and
its retention remain incomplete. Schematic capture covers the isolated DMX interface
and current power/buffer/POR/cutoff/SPI/service hardware. MCU/RF support is
captured separately;37 MCU/RF/DMX parts have partial placement. Complete PCB
placement/routing, USB protection qualification and mains source boards remain
unfinished RFQ/NRE work.

No vendor firmware, proprietary implementation, binaries or secrets are included.
Manufacturer datasheets consulted are linked in the canonical design and BOM.
No manufacturing order, hardware energization, purchase, branch change, commit or
push was performed by the design child. Parent integrates and publishes.

## Current power-only and RDM service hardware

Owner correction: “Thats fine, we can skip usb interop and just leave wireless AND wired RDM as the main path. The key is going to be how do we flash updates to the device over the DMX port”.

`eda/power-service/DESIGN.md` is the source/pin/budget record for this capture.
USB-C is power only; there is no onboard UART bridge or USB recovery domain.
`eda/historical/` preserves the superseded candidate and its old ERC evidence;
it is excluded from current package acceptance.

```sh
python3 hardware/compact-dmx/eda/power-service/generate.py
python3 hardware/compact-dmx/eda/power-service/verify.py
python3 hardware/compact-dmx/eda/generate_dmx_sheet.py
python3 hardware/compact-dmx/eda/verify_kicad.py
python3 hardware/compact-dmx/eda/power_budget.py
QT_QPA_PLATFORM=offscreen /home/juicebox/.local/bin/freecadcmd hardware/compact-dmx/cad/build_cad.py
python3 hardware/compact-dmx/cad/make_drawings.py
python3 hardware/compact-dmx/validate_package.py
```

The power/service generator produces self-contained modern KiCad source and a
matching library. Its verifier runs actual CLI export/ERC and independently
checks IC pins, every two-terminal component, USB-data NCs, latch states and
separation of resident-service and ROM straps. PDF/SVG and a component ledger
are actual KiCad exports/derived records. Four power flags identify implemented
passive-derived rails; none substitutes for a control gate.

The resident DMX/RDM update loader, rollback/authentication policy and factory
CCFG mapping are future software work, not implemented or tested here. The service
button is distinct from the ROM UART/SPI backdoor. cJTAG and ROM/reset factory pads
remain. Stable VBUS and power-good are exposed; capacitor energy is ride-through,
not a whole-transfer guarantee. No MCU GPIO pin number is invented.

`eda/power-budget.json` records the retained <=500mA PSD design basis,25mA charge setting,
current/cutoff tolerances and unmeasured runtime. Existing98x34x24mm housing is
retained; the SPI NOR max envelope replaces the bridge, but the complete power
component placement does not yet fit a verified25x6mm allocation.

### MCU support and dual-band frontend follow-up

`eda/mcu-radio/` now captures exact CC1352R1 support values from public TI
SWRC354 Rev1.1.0 plus the production Johanson0900PC15A0036001E frontend.
Owner selected **2.4GHz plus US915MHz**; one shared radio, now with two antenna feeds. Run `python3 eda/mcu-radio/generate.py` then `python3 eda/mcu-radio/verify.py` from this directory. KiCad10.0.7 actual export/ERC verifies26 components,57 nets,49MCU contacts,46 retained TI reference connections and12 antenna-match connections, plus current power/DMX endpoint snapshots. Zero ERC violations does not qualify RF performance.

Johanson0900AD47A2450001E dual-feed prototype removes the preliminary Murata switch, its control resistor and common DC block. Its five matching parts use manufacturer reference values. The50×30mm reference board differs from our90×28mm board;18×28mm end-region reservation is only a placement proposal. Inactive-port loading/stress, tuning, fixture-metal clearance, crystal qualification and PCB routing remain gates. See [sources and limits](eda/mcu-radio/DESIGN.md), [reservations](eda/mcu-radio/placement-reservations.csv) and `dualfeed-implementation-receipt.json`. Older allocation/dualband receipts and `historical-switched/` are historical, outside current acceptance.

DIO4/pin9SERVICE remains separate from DIO3/pin8ROM. DIO18/pin28 fault reserve
remainsNC until a power-off-safe interface is agreed. R4 limits EN/FLT current;
The minimal prototype uses ISOW1412 on-chip ESD capability; no external SM712. Manual120ohm termination is now captured, assembledOFF. No firmware,
complete-product/ERC/PCB qualification or proven hardware recovery is claimed.

### Termination and partial source footprints

`eda/footprints/DESIGN.md` records the minimal component-ESD basis, manual termination ratings/derating and placement constraints. DMX exports14 components/15nets with zeroERC. `eda/footprints/generate.py` writes editable local lands; run its `verify.py` using `flatpak run --command=python3 org.kicad.KiCad`. The [RF replacement pass](eda/footprints/REPLACEMENT-PASS.md) gives36 source-backed assignments and one provisional switch across37 physical MCU/RF/DMX parts.17 footprints parse;16 dimensioned patterns/113 numbered pads are checked. IPC copper/paste/mask lands are exact TI reference vectors. Five matching parts now use source-backed Coilcraft/Murata lands, with RF retuning still required. PCM12SMTR is Active, but its mounting-row datum/pattern correction remains open; this is **not full footprint-source acceptance or a PCB release**. Current evidence is in `eda/footprints/replacement-receipt.json`; prior assignment receipts are historical.

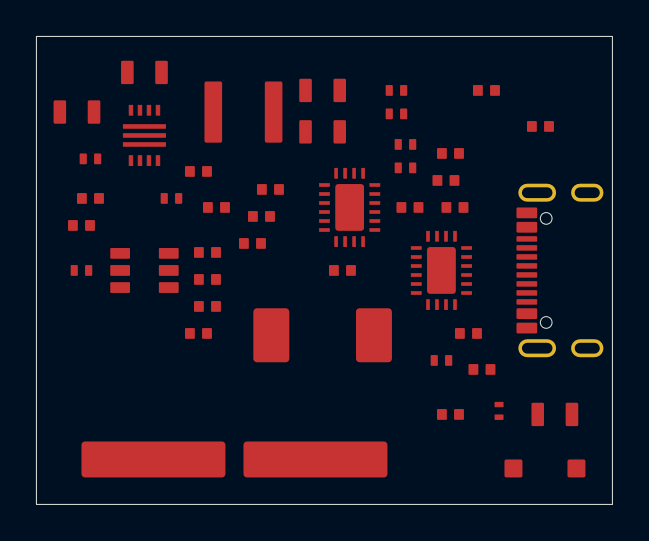
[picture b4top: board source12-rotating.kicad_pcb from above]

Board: 4 copper layers, 32.0 x 26.0 mm, 45 parts (0 on the bottom side), 24 nets, no tracks yet.

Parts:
C2, C3, C7: MSAST21GBB5106MTNA01 10uF; C0805
C4, C5: MSASE21GBB5226MTNA01 22uF; C0805
C6: T520D157M010ATE055 150uF; T520D
C8, C9, C15, C16, C17: TMK105B7104MV-FR 100nF; C0402
C10, C12, C13: GRM155R71E103KA01D 10nF; C0402
D1: TPD1E10B06DPYR; DPY2
J1: USB4105-GF-A; USB4105
J3: FAB_FPC20_ROTATING; FPC20
L1: XAL4020-152MEC 1.5uH; XAL4020
R7: TNPW040264K0BYED 64000ohm; R0402
R8, R10, R21, R27: TNPW040210K0BYED 10000ohm; R0402
R9, R11, R13, R15, R16, R17, R22, R23, R24, R25, R26: TNPW0402100KBYED 100000ohm; R0402
R12: TNPW04029K09BYED 9090ohm; R0402
R14: TNPW04028K00BYED 8000ohm; R0402
R18: TNPW040220K0BYED 20000ohm; R0402
R19: TNPW040224K9BYED 24900ohm; R0402
R20: TNPW040237K4BYED 37400ohm; R0402
TP1: FAB_PORT_FAULT_PROBE; TP1
TP2: FAB_PROTECT_FAULT_PROBE; TP1
U2: TPS62135RGXR; RGX11
U3: TPS25810RVCR; RVC20
U4: TPS25940LRVCR; RVC20
U5: TPS3700DDCR; DDC6

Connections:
BACKSTOP_OVP: R17.2, R18.1, U4.15
BARRIER_DVDT: C12.1, C13.1, U4.18
BARRIER_EN: R15.2, R16.1, U4.14, U5.1, U5.6
BARRIER_ILIM: R19.1, U4.17
BUCK5_18: C4.1, C5.1, C16.1, L1.2, R7.1, R11.1, R13.1, R15.1, R17.1, U2.6, U4.9, U4.10, U4.11, U4.12, U4.13
BUCK_OV_SENSE: R13.2, R14.1, U5.4
BUCK_UV_SENSE: R11.2, R12.1, U5.3
FPC12_PROTECTED: C2.1, C3.1, C9.1, C15.1, J3.1, R9.1, U2.1, U2.10, U5.5
GND_ISO: C2.2, C3.2, C4.2, C5.2, C6.2, C7.2, C8.2, C9.2, C10.2, C12.2, C13.2, C15.2, C16.2, C17.2, D1.2, J1.A1_B12, J1.B1_A12, J1.S1, J1.S2, J1.S3, J1.S4, J3.2, R8.2, R10.2, R12.2, R14.2, R16.2, R18.2, R19.2, R21.2, R23.2, R27.2, U2.3, U2.11, U3.8, U3.12, U3.21, U4.1, U4.16, U4.21, U5.2
PORT_ENABLE: R22.2, R23.1, U2.7, U3.6, U4.2
PORT_FAULT_N: R25.2, TP1.1, U3.1
PROTECT_FAULT_N: R26.2, TP2.1, U4.20
REF: R24.1, U3.10
REF_RTN: R24.2, U3.9
REG_EN: R9.2, R10.1, U2.8
REG_FB: R7.2, R8.1, U2.5
REG_SS: C10.1, U2.9
SAFE5_18: C6.1, C8.1, C17.1, R20.1, R22.1, R25.1, R26.1, R27.1, U3.2, U3.3, U3.4, U3.5, U3.7, U4.4, U4.5, U4.6, U4.7, U4.8
SAFE_PGTH: R20.2, R21.1, U4.3
SW: L1.1, U2.2
USB_CC1: J1.A5, U3.11
USB_CC2: J1.B5, U3.13
USB_D_SHORT: J1.A6, J1.A7, J1.B6, J1.B7
USB_VBUS: C7.1, D1.1, J1.A4_B9, J1.B4_A9, U3.14, U3.15
